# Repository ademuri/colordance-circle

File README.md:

# Colordance Circle

An art project that uses arrays of colored lights around a circle to create
kaleidoscopic colored shadows.

"This is not an officially supported Google product"

## Building

This project uses two build systems, PlatformIO and CMake. PIO is for code which
runs on embedded devices - these run the actual hardware. CMake is for running
tests on standard PCs.

To build with PlatformIO, run `pio run -e <env>`, where `<env>` is one defined
in [platformio.ini](platformio.ini) (e.g. `teensy`).

To run the tests:

```
mkdir -p build
cd build
cmake .. -DBUILD_SIMULATOR=false
make && ./generictest
```

### Simulator

The simulator uses SDL2 to render the LEDs. To build it, first install the SDL2 development library

`sudo apt install libsdl2-dev`

then, from the `build` directory, configure CMake to build it with

`cmake .. -DBUILD_SIMULATOR=true`

then build and run it with

`make && ./lib/simulator/Simulator`

#### Processing

To run the simulator with the Processing controller, from the build directory run:

```bash
${PROCESSING_HOME?}/processing-java --sketch=../controller/processing_controller --run | ./lib/simulator/Simulator
```

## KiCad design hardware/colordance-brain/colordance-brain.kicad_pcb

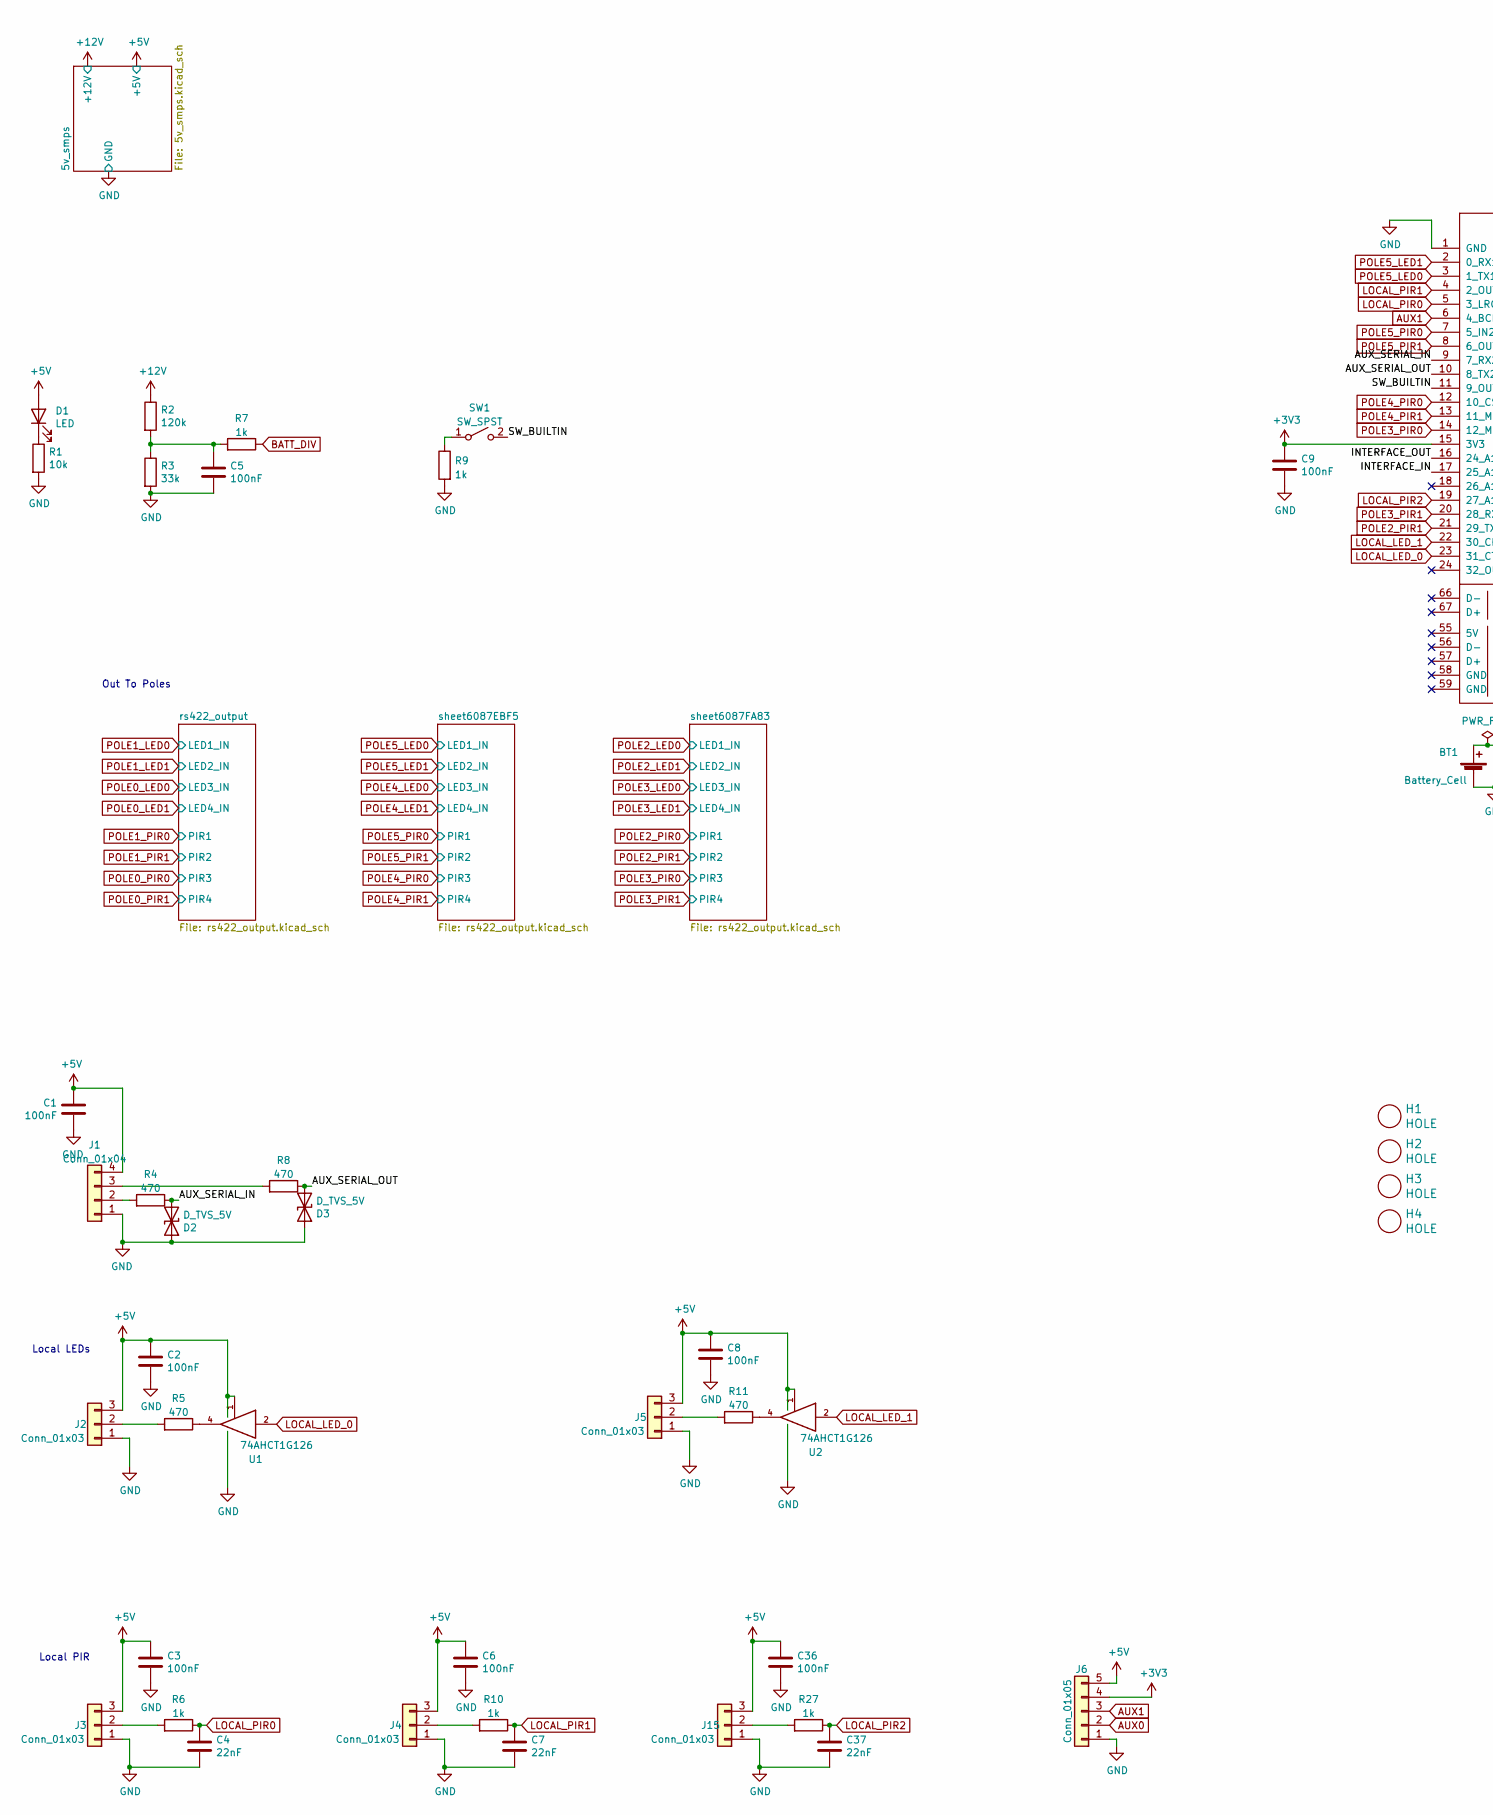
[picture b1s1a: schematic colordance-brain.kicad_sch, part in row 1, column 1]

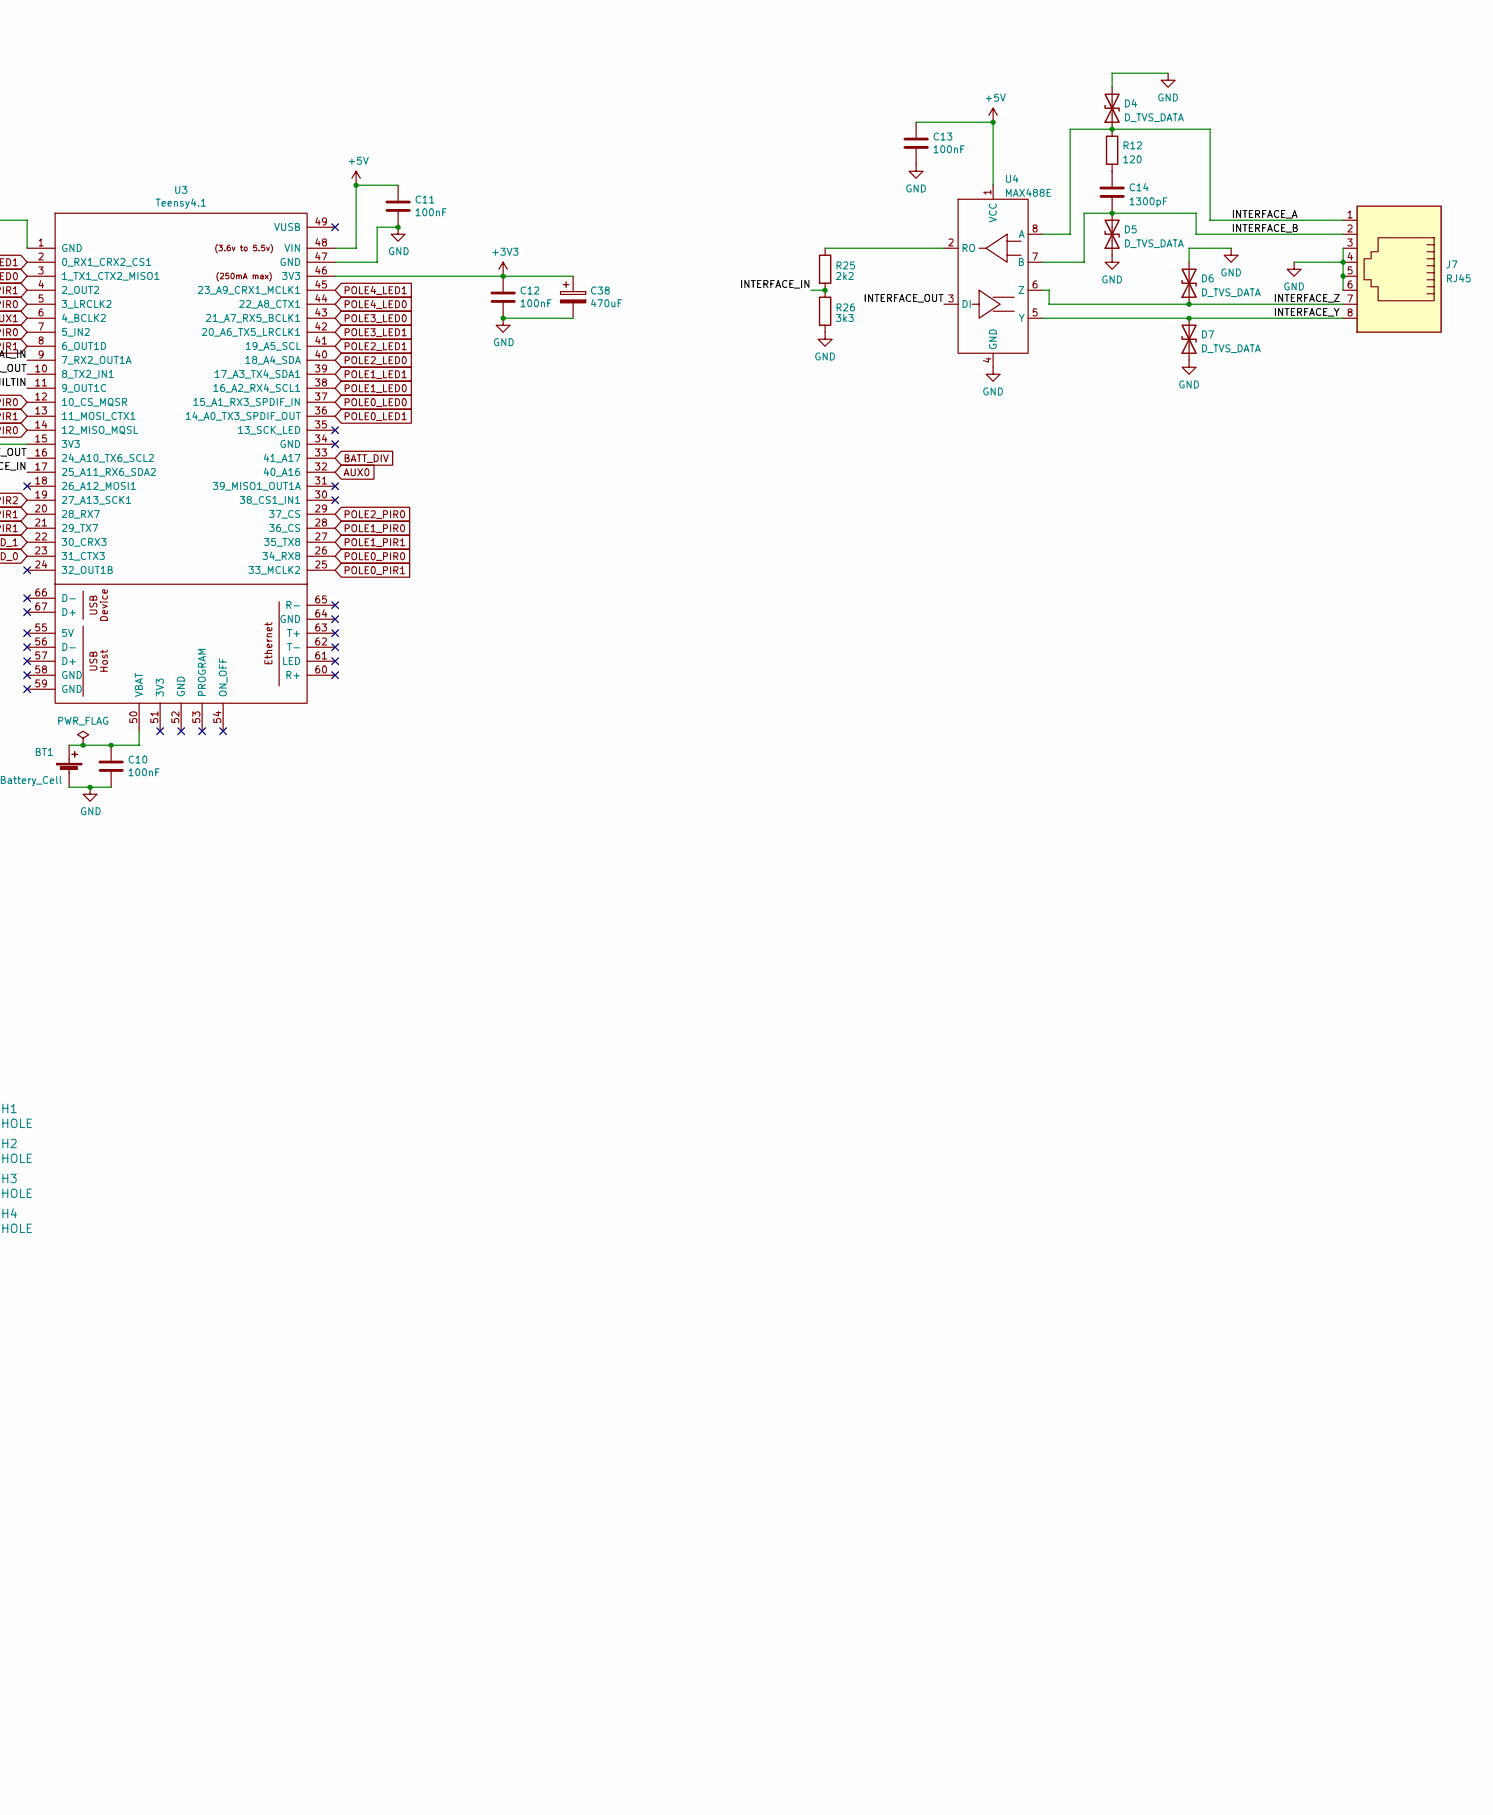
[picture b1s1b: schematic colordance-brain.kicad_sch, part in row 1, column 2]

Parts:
BT1: Battery_Cell; BatteryHolder_Keystone_3034_1x20mm; MPN 3034
C1, C2, C3, C5, C6, C8, C9, C10, C11, C12, C13, C36: 100nF; C_0402_1005Metric; LCSC C307331
C4, C7, C37: 22nF; C_0603_1608Metric; LCSC C21122
C14: 1300pF; C_0603_1608Metric; LCSC C1595
C38: 470uF; CP_Radial_D10.0mm_P5.00mm; MPN ESC477M035AH4EA
D1: LED; LED_0603_1608Metric; MPN 150060RS75000; LCSC C2286
D2, D3: D_TVS_5V; D_SMB; MPN SMBJ6.0CD-M3/H; LCSC C78395
D4, D5, D6, D7: D_TVS_DATA; D_SMB; MPN SMBJ6.0CD-M3/H; LCSC C78395
H1, H2, H3, H4: HOLE; HOLE_5MM_#8
J1: Conn_01x04; PinHeader_1x04_P2.54mm_Horizontal
J2, J3, J4, J5, J15: Conn_01x03; PinHeader_1x03_P2.54mm_Horizontal; MPN 78208-103HLF
J6: Conn_01x05; PinHeader_1x05_P2.54mm_Horizontal
J7: RJ45; RJ45_Amphenol_54602-x08_Horizontal; MPN 54601-908WPLF
R1: 10k; R_0603_1608Metric; LCSC C25804
R2: 120k; R_0603_1608Metric; MPN RG2012P-125-B-T5; LCSC C25808
R3: 33k; R_0603_1608Metric; MPN RT0603BRD07330KL; LCSC C4216
R4, R5, R8, R11: 470; R_0603_1608Metric; LCSC C23179
R6, R7, R9, R10, R27: 1k; R_0603_1608Metric; LCSC C21190
R12: 120; R_0603_1608Metric; LCSC C22787
R25: 2k2; R_0603_1608Metric; LCSC C4190
R26: 3k3; R_0603_1608Metric; LCSC C22978
SW1: SW_SPST; SW_PUSH_6mm
U1, U2: 74AHCT1G126; SOT-23-5; MPN 74AHCT1G126SE-7; LCSC C163712
U3: Teensy4.1; Teensy41_stripped; MPN PPPC241LFBN-RC
U4: MAX488E; SOIC-8_3.9x4.9mm_P1.27mm; LCSC C10919

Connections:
+3V3: C9.1, C12.1, C38.1, J6.4, U3.15 (3V3), U3.46 (3V3)
+5V: C1.1, C2.1, C3.1, C6.1, C8.1, C11.1, C13.1, C36.1, D1.2 (A), J1.4, J2.3, J3.3, J4.3, J5.3, J6.5, J15.3, U1.1, U1.5 (VCC), U2.1, U2.5 (VCC), U3.48 (VIN), U4.1 (VCC); also elsewhere on the board
+12V: R2.1; also elsewhere on the board
/AUX_SERIAL_IN: D2.2 (A2), R4.1, U3.9 (7_RX2_OUT1A)
/AUX_SERIAL_OUT: D3.2 (A2), R8.1, U3.10 (8_TX2_IN1)
/INTERFACE_A: D4.1 (A1), J7.1, R12.1, U4.8 (A)
/INTERFACE_B: C14.2, D5.2 (A2), J7.2, U4.7 (B)
/INTERFACE_IN: R25.2, R26.1, U3.17 (25_A11_RX6_SDA2)
/INTERFACE_OUT: U3.16 (24_A10_TX6_SCL2), U4.3 (DI)
/INTERFACE_Y: D7.2 (A2), J7.8, U4.5 (Y)
/INTERFACE_Z: D6.1 (A1), J7.7, U4.6 (Z)
/SW_BUILTIN: SW1.2 (B), U3.11 (9_OUT1C)
AUX0: J6.2, U3.32 (40_A16)
AUX1: J6.3, U3.6 (4_BCLK2)
BATT_DIV: R7.1, U3.33 (41_A17)
GND: BT1.2 (-), C1.2, C2.2, C3.2, C4.2, C5.2, C6.2, C7.2, C8.2, C9.2, C10.2, C11.2, C12.2, C13.2, C36.2, C37.2, C38.2, D2.1 (A1), D3.1 (A1), D4.2 (A2), D5.1 (A1), D6.2 (A2), D7.1 (A1), J1.1, J2.1, J3.1, J4.1, J5.1, J6.1, J7.3, J7.4, J7.5, J7.6, J15.1, R1.2, R3.2, R9.2, R26.2, U1.3 (GND), U2.3 (GND), U3.1 (GND), U3.47 (GND), U4.4 (GND); also elsewhere on the board
LOCAL_LED_0: U1.2, U3.23 (31_CTX3)
LOCAL_LED_1: U2.2, U3.22 (30_CRX3)
LOCAL_PIR0: C4.1, R6.1, U3.5 (3_LRCLK2)
LOCAL_PIR1: C7.1, R10.1, U3.4 (2_OUT2)
LOCAL_PIR2: C37.1, R27.1, U3.19 (27_A13_SCK1)
unnamed: BT1.1 (+), C10.1, U3.50 (VBAT)
unnamed: C5.1, R2.2, R3.1, R7.2
unnamed: C14.1, R12.2
unnamed: D1.1 (K), R1.1
unnamed: J1.2, R4.2
unnamed: J1.3, R8.2
unnamed: J2.2, R5.2
unnamed: J3.2, R6.2
unnamed: J4.2, R10.2
unnamed: J5.2, R11.2
unnamed: J15.2, R27.2
unnamed: R5.1, U1.4
unnamed: R11.1, U2.4
unnamed: R9.1, SW1.1 (A)
unnamed: R25.1, U4.2 (RO)
POLE0_LED0: U3.37 (15_A1_RX3_SPDIF_IN); also elsewhere on the board
POLE0_LED1: U3.36 (14_A0_TX3_SPDIF_OUT); also elsewhere on the board
POLE0_PIR0: U3.26 (34_RX8); also elsewhere on the board
POLE0_PIR1: U3.25 (33_MCLK2); also elsewhere on the board
POLE1_LED0: U3.38 (16_A2_RX4_SCL1); also elsewhere on the board
POLE1_LED1: U3.39 (17_A3_TX4_SDA1); also elsewhere on the board
POLE1_PIR0: U3.28 (36_CS); also elsewhere on the board
POLE1_PIR1: U3.27 (35_TX8); also elsewhere on the board
POLE2_LED0: U3.40 (18_A4_SDA); also elsewhere on the board
POLE2_LED1: U3.41 (19_A5_SCL); also elsewhere on the board
POLE2_PIR0: U3.29 (37_CS); also elsewhere on the board
POLE2_PIR1: U3.21 (29_TX7); also elsewhere on the board
POLE3_LED0: U3.43 (21_A7_RX5_BCLK1); also elsewhere on the board
POLE3_LED1: U3.42 (20_A6_TX5_LRCLK1); also elsewhere on the board
POLE3_PIR0: U3.14 (12_MISO_MQSL); also elsewhere on the board
POLE3_PIR1: U3.20 (28_RX7); also elsewhere on the board
POLE4_LED0: U3.44 (22_A8_CTX1); also elsewhere on the board
POLE4_LED1: U3.45 (23_A9_CRX1_MCLK1); also elsewhere on the board
POLE4_PIR0: U3.12 (10_CS_MQSR); also elsewhere on the board
POLE4_PIR1: U3.13 (11_MOSI_CTX1); also elsewhere on the board
POLE5_LED0: U3.3 (1_TX1_CTX2_MISO1); also elsewhere on the board
POLE5_LED1: U3.2 (0_RX1_CRX2_CS1); also elsewhere on the board
POLE5_PIR0: U3.7 (5_IN2); also elsewhere on the board
POLE5_PIR1: U3.8 (6_OUT1D); also elsewhere on the board

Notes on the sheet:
Local LEDs
Out To Poles
Local PIR

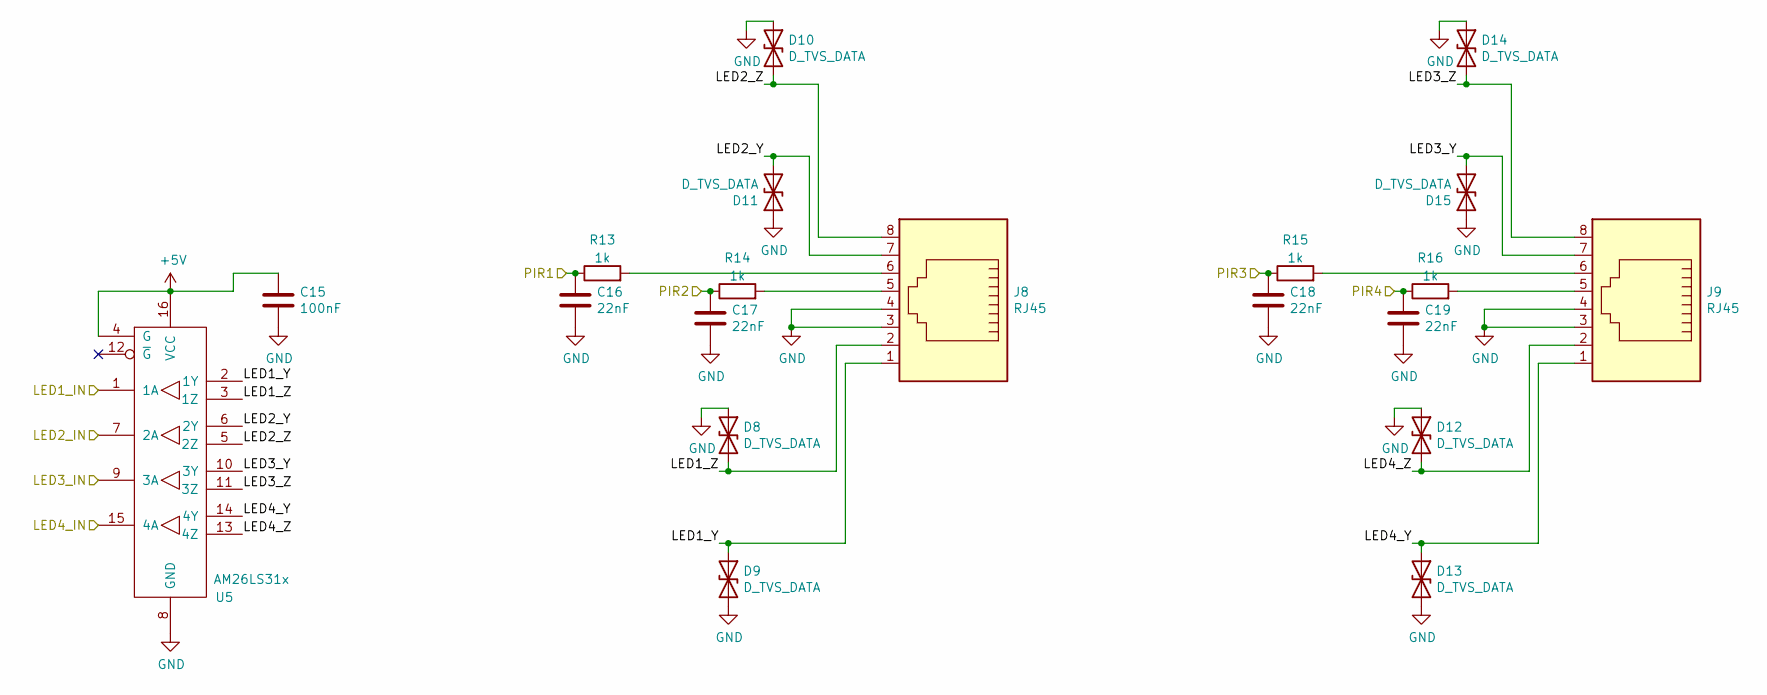
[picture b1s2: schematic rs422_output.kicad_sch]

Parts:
C15: 100nF; C_0402_1005Metric; LCSC C307331
C16, C17, C18, C19: 22nF; C_0603_1608Metric; LCSC C21122
D8, D9, D10, D11, D12, D13, D14, D15: D_TVS_DATA; D_SMB; MPN SMBJ6.0CD-M3/H; LCSC C78395
J8, J9: RJ45; RJ45_Amphenol_54602-x08_Horizontal; MPN 54601-908WPLF
R13, R14, R15, R16: 1k; R_0603_1608Metric; LCSC C21190
U5: AM26LS31x; SOIC-16_3.9x9.9mm_P1.27mm; MPN AM26LS31CDR; LCSC C6179

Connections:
+5V: C15.1, U5.4 (G), U5.16 (VCC); also elsewhere on the board
/rs422_output/LED1_Y: D9.1 (A1), J8.1, U5.2 (1Y)
/rs422_output/LED1_Z: D8.2 (A2), J8.2, U5.3 (1Z)
/rs422_output/LED2_Y: D11.2 (A2), J8.7, U5.6 (2Y)
/rs422_output/LED2_Z: D10.2 (A2), J8.8, U5.5 (2Z)
/rs422_output/LED3_Y: D15.2 (A2), J9.7, U5.10 (3Y)
/rs422_output/LED3_Z: D14.2 (A2), J9.8, U5.11 (3Z)
/rs422_output/LED4_Y: D13.1 (A1), J9.1, U5.14 (4Y)
/rs422_output/LED4_Z: D12.2 (A2), J9.2, U5.13 (4Z)
GND: C15.2, C16.2, C17.2, C18.2, C19.2, D8.1 (A1), D9.2 (A2), D10.1 (A1), D11.1 (A1), D12.1 (A1), D13.2 (A2), D14.1 (A1), D15.1 (A1), J8.3, J8.4, J9.3, J9.4, U5.8 (GND); also elsewhere on the board
unnamed: J8.5, R14.2
unnamed: J8.6, R13.2
unnamed: J9.5, R16.2
unnamed: J9.6, R15.2
POLE0_LED0: U5.9 (3A); also elsewhere on the board
POLE0_LED1: U5.15 (4A); also elsewhere on the board
POLE0_PIR0: C18.1, R15.1; also elsewhere on the board
POLE0_PIR1: C19.1, R16.1; also elsewhere on the board
POLE1_LED0: U5.1 (1A); also elsewhere on the board
POLE1_LED1: U5.7 (2A); also elsewhere on the board
POLE1_PIR0: C16.1, R13.1; also elsewhere on the board
POLE1_PIR1: C17.1, R14.1; also elsewhere on the board

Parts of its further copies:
C20, C25: 100nF; C_0402_1005Metric; LCSC C307331
C21, C22, C23, C24, C26, C27, C28, C29: 22nF; C_0603_1608Metric; LCSC C21122
D16, D17, D18, D19, D20, D21, D22, D23, D24, D25, D26, D27, D28, D29, D30, D31: D_TVS_DATA; D_SMB; MPN SMBJ6.0CD-M3/H; LCSC C78395
J10, J11, J12, J13: RJ45; RJ45_Amphenol_54602-x08_Horizontal; MPN 54601-908WPLF
R17, R18, R19, R20, R21, R22, R23, R24: 1k; R_0603_1608Metric; LCSC C21190
U6, U7: AM26LS31x; SOIC-16_3.9x9.9mm_P1.27mm; MPN AM26LS31CDR; LCSC C6179

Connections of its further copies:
+5V: C20.1, C25.1, U6.4 (G), U6.16 (VCC), U7.4 (G), U7.16 (VCC); also elsewhere on the board
/sheet6087EBF5/LED1_Y: D17.1 (A1), J10.1, U6.2 (1Y)
/sheet6087EBF5/LED1_Z: D16.2 (A2), J10.2, U6.3 (1Z)
/sheet6087EBF5/LED2_Y: D19.2 (A2), J10.7, U6.6 (2Y)
/sheet6087EBF5/LED2_Z: D18.2 (A2), J10.8, U6.5 (2Z)
/sheet6087EBF5/LED3_Y: D23.2 (A2), J11.7, U6.10 (3Y)
/sheet6087EBF5/LED3_Z: D22.2 (A2), J11.8, U6.11 (3Z)
/sheet6087EBF5/LED4_Y: D21.1 (A1), J11.1, U6.14 (4Y)
/sheet6087EBF5/LED4_Z: D20.2 (A2), J11.2, U6.13 (4Z)
/sheet6087FA83/LED1_Y: D25.1 (A1), J12.1, U7.2 (1Y)
/sheet6087FA83/LED1_Z: D24.2 (A2), J12.2, U7.3 (1Z)
/sheet6087FA83/LED2_Y: D27.2 (A2), J12.7, U7.6 (2Y)
/sheet6087FA83/LED2_Z: D26.2 (A2), J12.8, U7.5 (2Z)
/sheet6087FA83/LED3_Y: D31.2 (A2), J13.7, U7.10 (3Y)
/sheet6087FA83/LED3_Z: D30.2 (A2), J13.8, U7.11 (3Z)
/sheet6087FA83/LED4_Y: D29.1 (A1), J13.1, U7.14 (4Y)
/sheet6087FA83/LED4_Z: D28.2 (A2), J13.2, U7.13 (4Z)
GND: C20.2, C21.2, C22.2, C23.2, C24.2, C25.2, C26.2, C27.2, C28.2, C29.2, D16.1 (A1), D17.2 (A2), D18.1 (A1), D19.1 (A1), D20.1 (A1), D21.2 (A2), D22.1 (A1), D23.1 (A1), D24.1 (A1), D25.2 (A2), D26.1 (A1), D27.1 (A1), D28.1 (A1), D29.2 (A2), D30.1 (A1), D31.1 (A1), J10.3, J10.4, J11.3, J11.4, J12.3, J12.4, J13.3, J13.4, U6.8 (GND), U7.8 (GND); also elsewhere on the board
unnamed: J10.5, R18.2
unnamed: J10.6, R17.2
unnamed: J11.5, R20.2
unnamed: J11.6, R19.2
unnamed: J12.5, R22.2
unnamed: J12.6, R21.2
unnamed: J13.5, R24.2
unnamed: J13.6, R23.2
POLE2_LED0: U7.1 (1A); also elsewhere on the board
POLE2_LED1: U7.7 (2A); also elsewhere on the board
POLE2_PIR0: C26.1, R21.1; also elsewhere on the board
POLE2_PIR1: C27.1, R22.1; also elsewhere on the board
POLE3_LED0: U7.9 (3A); also elsewhere on the board
POLE3_LED1: U7.15 (4A); also elsewhere on the board
POLE3_PIR0: C28.1, R23.1; also elsewhere on the board
POLE3_PIR1: C29.1, R24.1; also elsewhere on the board
POLE4_LED0: U6.9 (3A); also elsewhere on the board
POLE4_LED1: U6.15 (4A); also elsewhere on the board
POLE4_PIR0: C23.1, R19.1; also elsewhere on the board
POLE4_PIR1: C24.1, R20.1; also elsewhere on the board
POLE5_LED0: U6.1 (1A); also elsewhere on the board
POLE5_LED1: U6.7 (2A); also elsewhere on the board
POLE5_PIR0: C21.1, R17.1; also elsewhere on the board
POLE5_PIR1: C22.1, R18.1; also elsewhere on the board

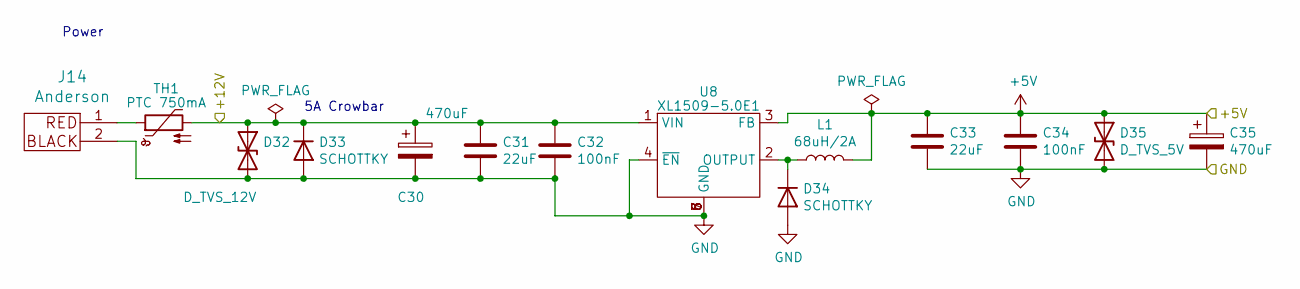
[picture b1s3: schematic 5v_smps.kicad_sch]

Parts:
C30, C35: 470uF; CP_Radial_D10.0mm_P5.00mm; MPN ESC477M035AH4EA
C31, C33: 22uF; C_0805_2012Metric; MPN LMK212BBJ226MG-T; LCSC C45783
C32, C34: 100nF; C_0402_1005Metric; LCSC C307331
D32: D_TVS_12V; D_SMB; MPN SMBJ13CA; LCSC C1976713
D33, D34: SCHOTTKY; D_SMA; LCSC C22452
D35: D_TVS_5V; D_SMB; MPN SMBJ6.0CD-M3/H; LCSC C78395
J14: Anderson; Anderson_1336G1_right_angle_bottom_two
L1: 68uH/2A; L_PROD-Tech_PSPMAA0805; LCSC C2962891
TH1: PTC 750mA; Fuse_1812_4532Metric; LCSC C20997
U8: XL1509-5.0E1; SOIC-8_3.9x4.9mm_P1.27mm; LCSC C61063

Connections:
+5V: C33.1, C34.1, C35.1, D35.1 (A1), L1.2, U8.3 (FB); also elsewhere on the board
+12V: C30.1, C31.1, C32.1, D32.1 (A1), D33.1 (K), TH1.2, U8.1 (VIN); also elsewhere on the board
GND: C30.2, C31.2, C32.2, C33.2, C34.2, C35.2, D32.2 (A2), D33.2 (A), D34.2 (A), D35.2 (A2), J14.2, U8.4 (~EN), U8.5 (GND), U8.6 (GND), U8.7 (GND), U8.8 (GND); also elsewhere on the board
unnamed: D34.1 (K), L1.1, U8.2 (OUTPUT)
unnamed: J14.1, TH1.1

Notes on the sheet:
Power
5A Crowbar

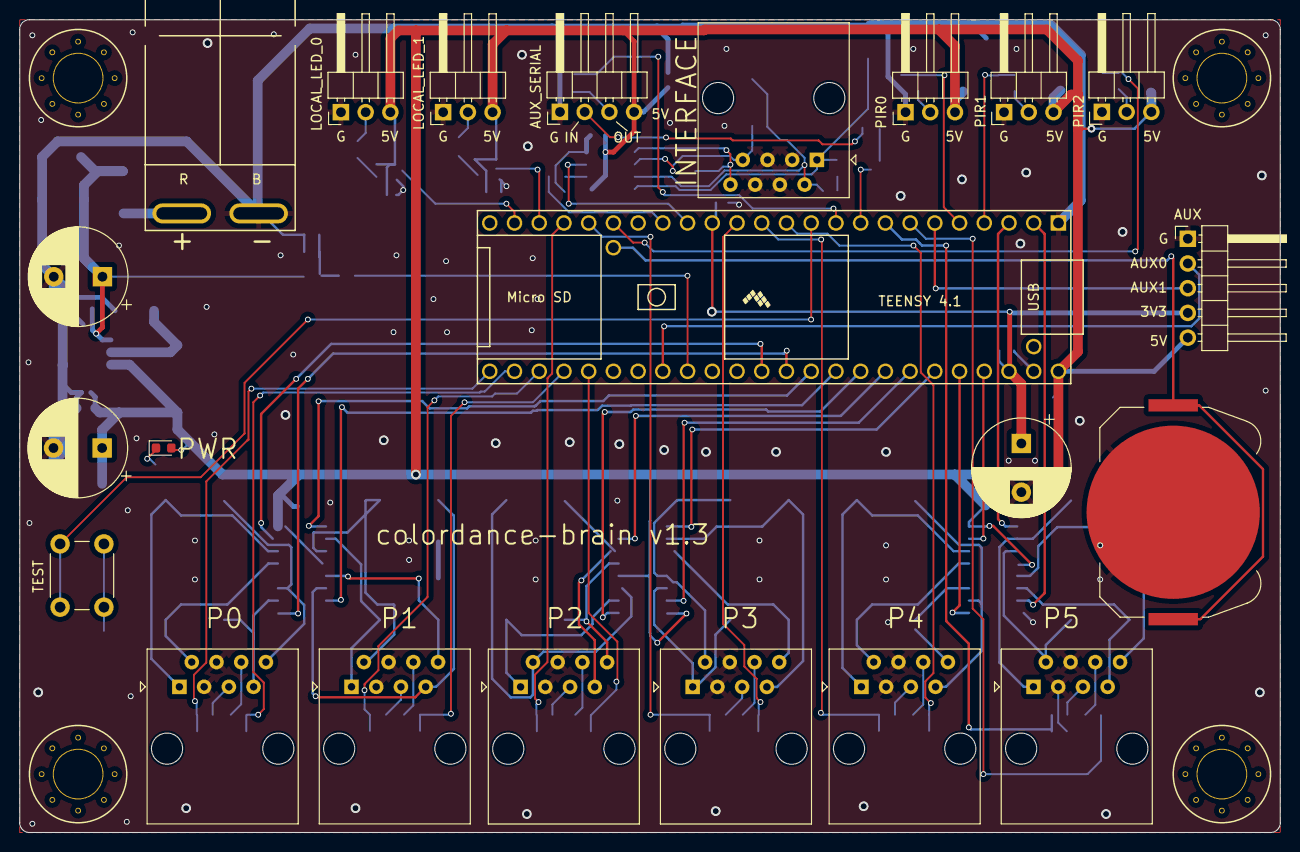
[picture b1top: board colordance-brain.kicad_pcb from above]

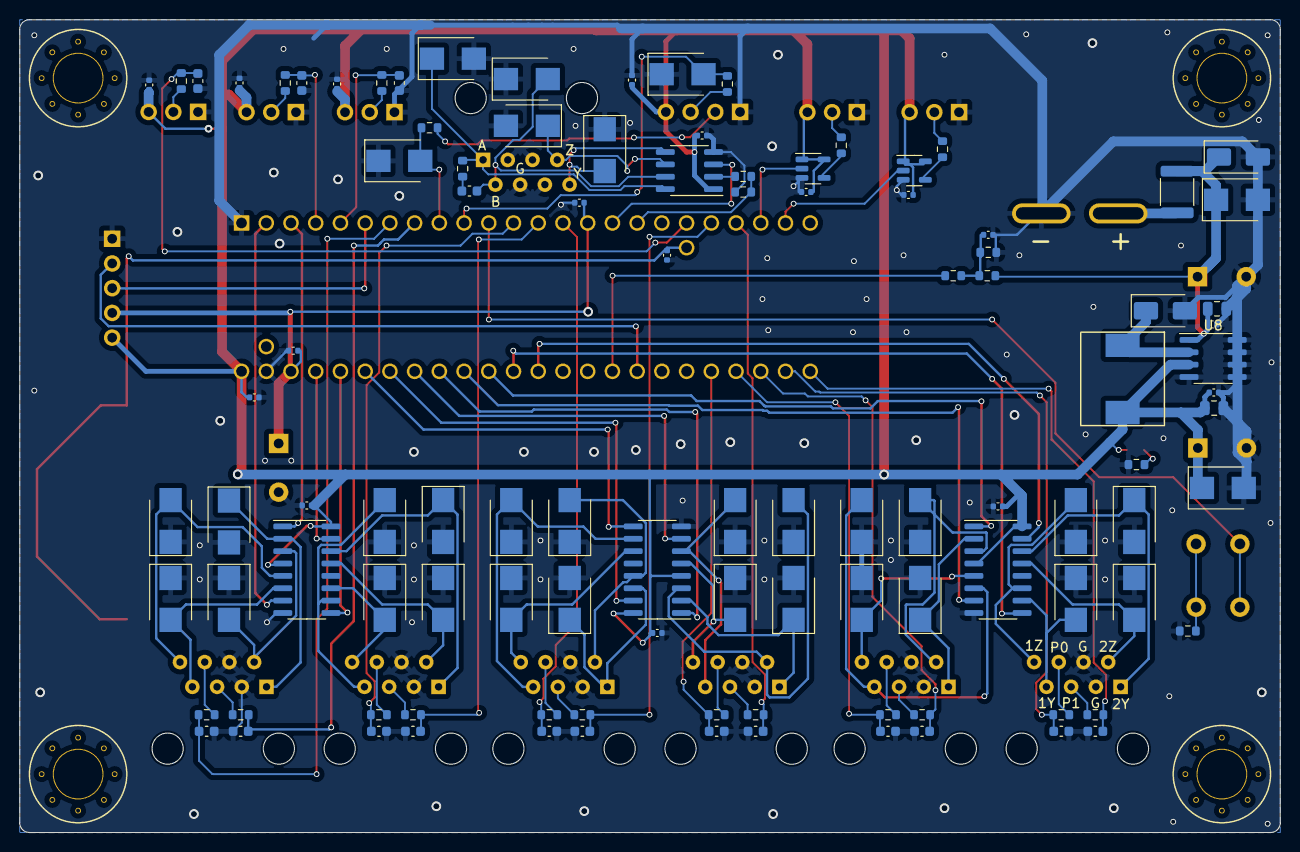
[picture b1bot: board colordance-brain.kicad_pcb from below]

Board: 2 copper layers, 129.5 x 83.5 mm, 131 parts (105 on the bottom side), 98 nets.

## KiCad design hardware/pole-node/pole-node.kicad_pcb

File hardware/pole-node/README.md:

## Datasheets

- APA3211: [datasheet](https://www.diodes.com/assets/Datasheets/AP3211.pdf), [application notes](https://www.diodes.com/assets/Part-Support-Files/AP3211/6434133.pdf)

## Calculations

### Voltage regulator

- Feedback voltage is 0.81V. Use [this voltage divider calculator](http://www.ti.com/download/kbase/volt/volt_div3.htm). For E96, this yields 11500 and 2210 Ohms, which produces 5.02v.
- Inductor value: `L1 = 5V * (12V - 5V) / (1.4MHz * 12V * 1.5A * .26) = 5.3uH -> 5.6 uH`
- Peak inductor current: `1.5A + ((12V - 5V) * 5V) / (2 * 1.4MHz * 12V * 5.6uH) = 1.69A`
- Inductor current rating is `1.5 * 1.69A = 2.5A`
- Input ripple with 10uF cap: `1.5A / (1.4Mhz * 10uF) * (5V / 12V) * (1 - (5V / 12V)) = .026V`

### RS485 termination

- [Application note](http://www.ti.com/lit/an/snla034b/snla034b.pdf)
- AC termination should yield clean signal without significantly increasing power consumption
- Assuming 40' max cable length:
- `C<sub>T <= (40ft * 2 * 1.7ns/ft) / 100 Ohm = 1.36 nF`
- This yields an RC time constant of `136 ns`. At `800 kHz`, the signal period is `1.25 us`.

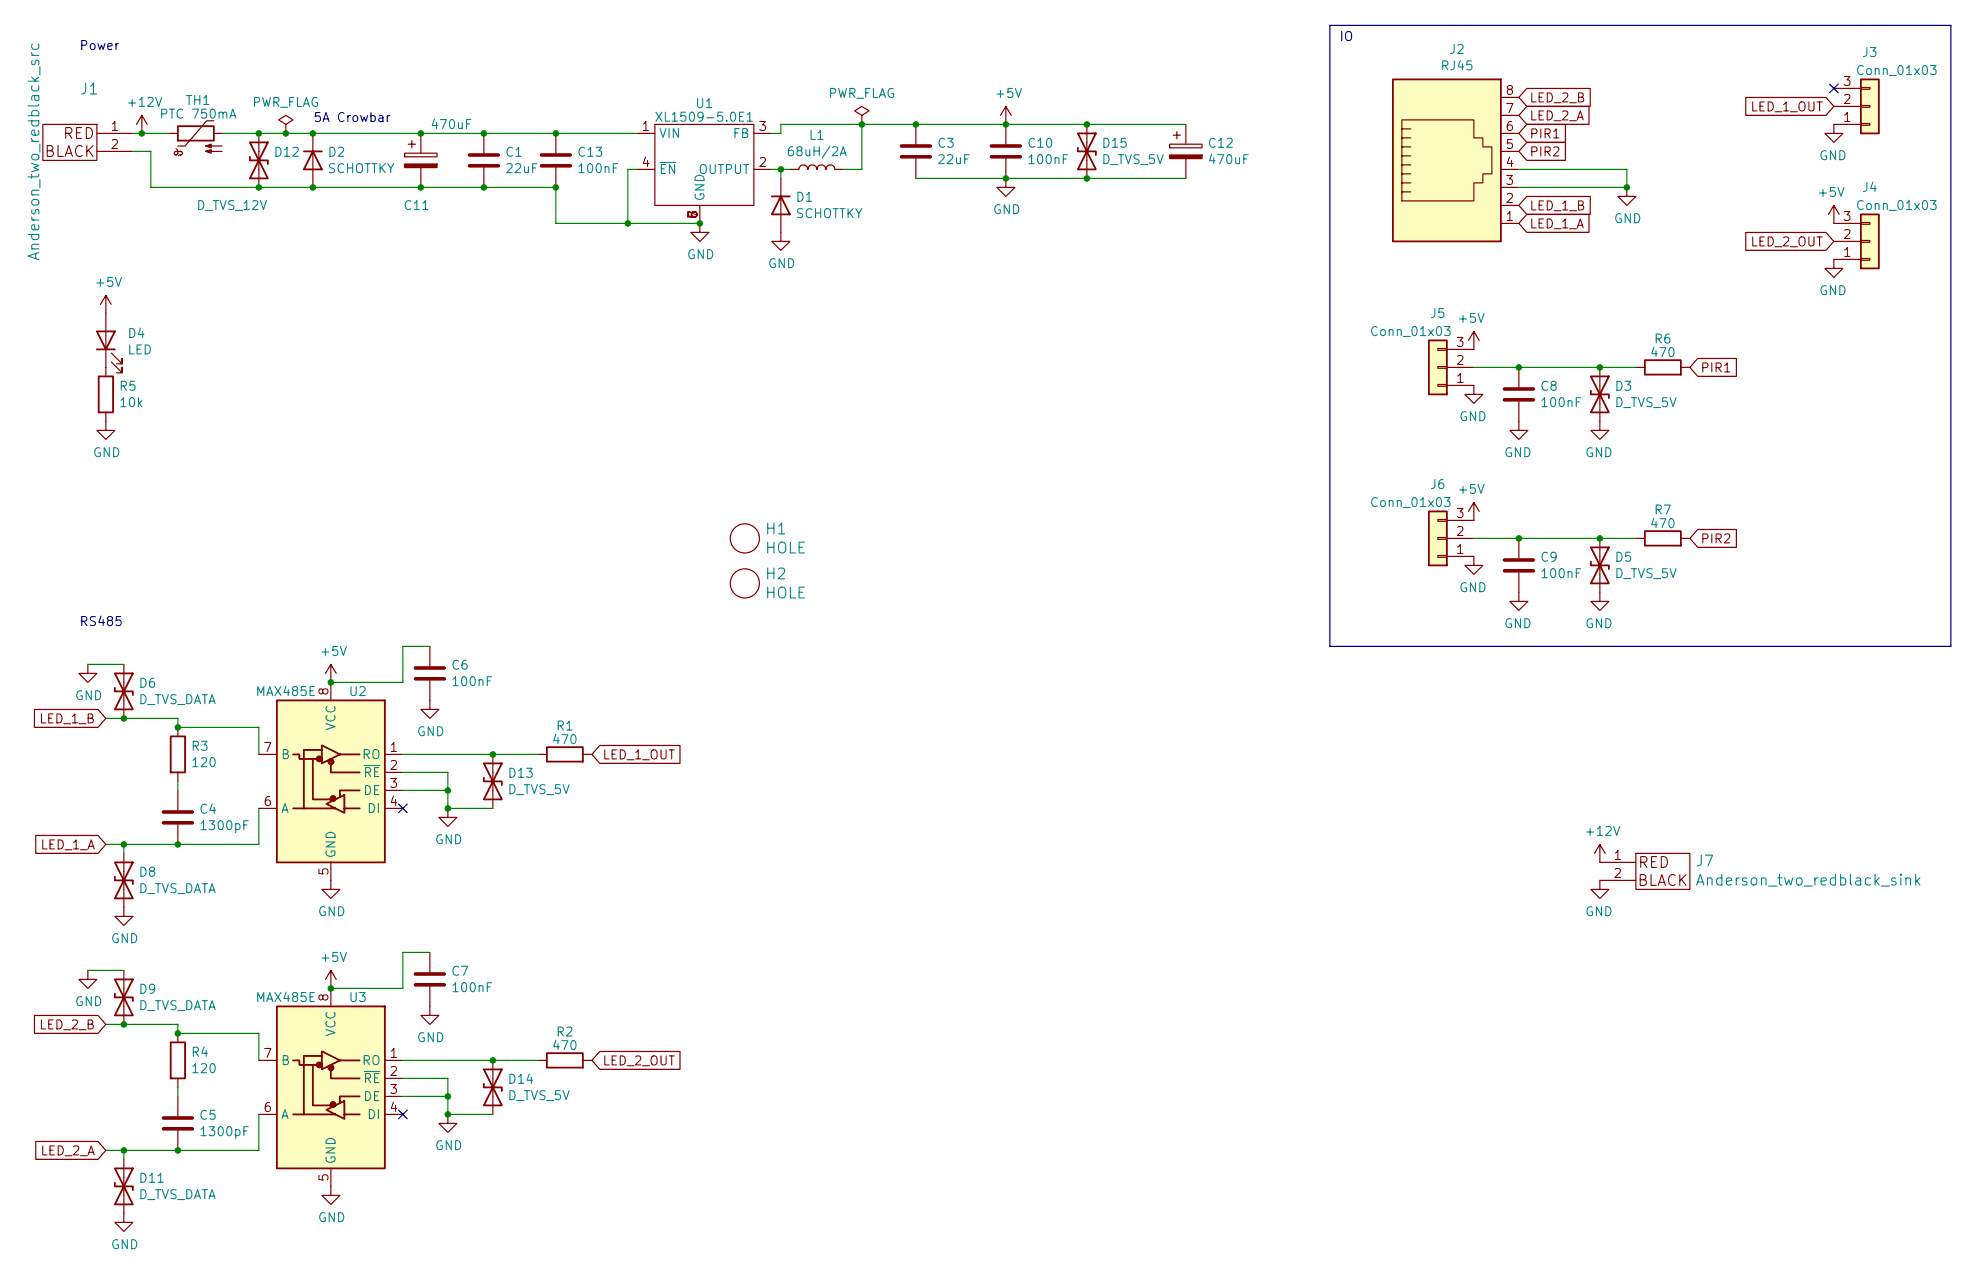
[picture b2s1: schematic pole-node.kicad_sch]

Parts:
C1, C3: 22uF; C_0805_2012Metric; MPN LMK212BBJ226MG-T; LCSC C45783
C4, C5: 1300pF; C_0603_1608Metric; MPN CL10B122KB8NNNC; LCSC C1595
C6, C7, C8, C9, C10, C13: 100nF; C_0402_1005Metric; LCSC C307331
C11, C12: 470uF; CP_Radial_D10.0mm_P5.00mm; MPN ESC477M035AH4EA
D1, D2: SCHOTTKY; D_SMA; LCSC C22452
D3, D5, D13, D14, D15: D_TVS_5V; D_SMB; MPN SMBJ6.0CD-M3/H; LCSC C78395
D4: LED; LED_0603_1608Metric; MPN 150060RS75000; LCSC C2286
D6, D8, D9, D11: D_TVS_DATA; D_SMB; MPN SMBJ6.0CD-M3/H; LCSC C78395
D12: D_TVS_12V; D_SMB; MPN SMBJ13CA; LCSC C1976713
H1, H2: HOLE
J1: Anderson_two_redblack_src
J2: RJ45; RJ45_Amphenol_54602-x08_Horizontal; MPN 54601-908WPLF
J3, J4, J5, J6: Conn_01x03; PinHeader_1x03_P2.54mm_Horizontal; MPN 78208-103HLF
J7: Anderson_two_redblack_sink
L1: 68uH/2A; L_PROD-Tech_PSPMAA0805; LCSC C2962891
R1, R2, R6, R7: 470; R_0603_1608Metric; LCSC C23179
R3, R4: 120; R_0603_1608Metric; MPN RMCF0603JG120R; LCSC C22787
R5: 10k; R_0603_1608Metric; LCSC C25804
TH1: PTC 750mA; Fuse_1812_4532Metric; LCSC C20997
U1: XL1509-5.0E1; SOIC-8_3.9x4.9mm_P1.27mm; LCSC C61063
U2, U3: MAX485E; SOIC-8_3.9x4.9mm_P1.27mm; MPN SP485ECN-L/TR; LCSC C916163

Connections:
+5V: C3.1, C6.1, C7.1, C10.1, C12.1, D4.2 (A), D15.1 (A1), J4.3, J5.3, J6.3, L1.2, U1.3 (FB), U2.8 (VCC), U3.8 (VCC)
+12V: J1.1, J7.1, TH1.1
GND: C1.2, C3.2, C6.2, C7.2, C8.2, C9.2, C10.2, C11.2, C12.2, C13.2, D1.2 (A), D2.2 (A), D3.2 (A2), D5.2 (A2), D6.1 (A1), D8.2 (A2), D9.1 (A1), D11.2 (A2), D12.2 (A2), D13.2 (A2), D14.2 (A2), D15.2 (A2), J1.2, J2.3, J2.4, J3.1, J4.1, J5.1, J6.1, J7.2, R5.2, U1.4 (~EN), U1.5 (GND), U1.6 (GND), U1.7 (GND), U1.8 (GND), U2.2 (~RE), U2.3 (DE), U2.5 (GND), U3.2 (~RE), U3.3 (DE), U3.5 (GND)
LED_1_A: C4.2, D8.1 (A1), J2.1, U2.6 (A)
LED_1_B: D6.2 (A2), J2.2, R3.1, U2.7 (B)
LED_1_OUT: J3.2, R1.2
LED_2_A: C5.2, D11.1 (A1), J2.7, U3.6 (A)
LED_2_B: D9.2 (A2), J2.8, R4.1, U3.7 (B)
LED_2_OUT: J4.2, R2.2
unnamed: C1.1, C11.1, C13.1, D2.1 (K), D12.1 (A1), TH1.2, U1.1 (VIN)
unnamed: C4.1, R3.2
unnamed: C5.1, R4.2
unnamed: D1.1 (K), L1.1, U1.2 (OUTPUT)
unnamed: C8.1, D3.1 (A1), J5.2, R6.1
unnamed: D4.1 (K), R5.1
unnamed: C9.1, D5.1 (A1), J6.2, R7.1
unnamed: D13.1 (A1), R1.1, U2.1 (RO)
unnamed: D14.1 (A1), R2.1, U3.1 (RO)
PIR1: J2.6, R6.2
PIR2: J2.5, R7.2

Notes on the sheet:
Power
5A Crowbar
RS485

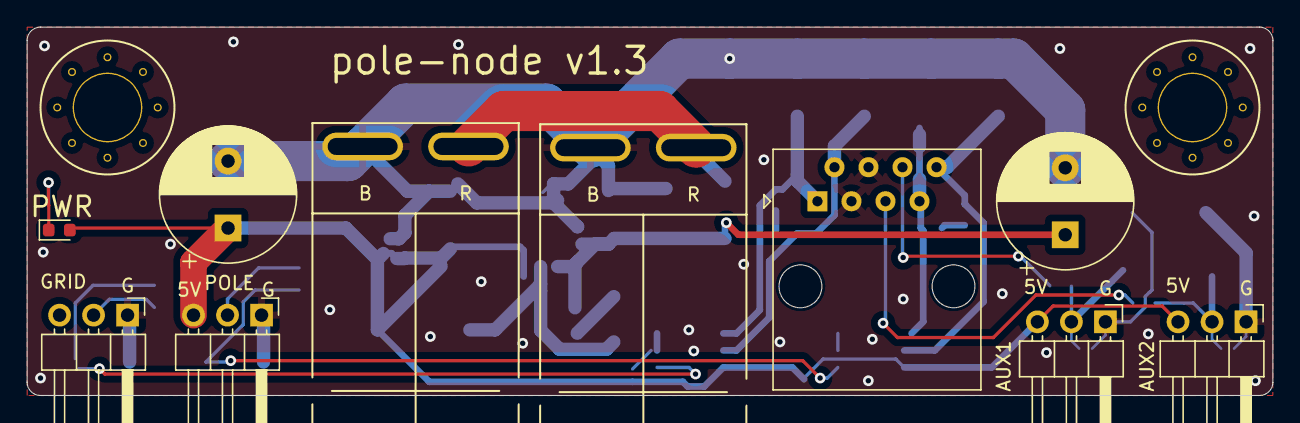
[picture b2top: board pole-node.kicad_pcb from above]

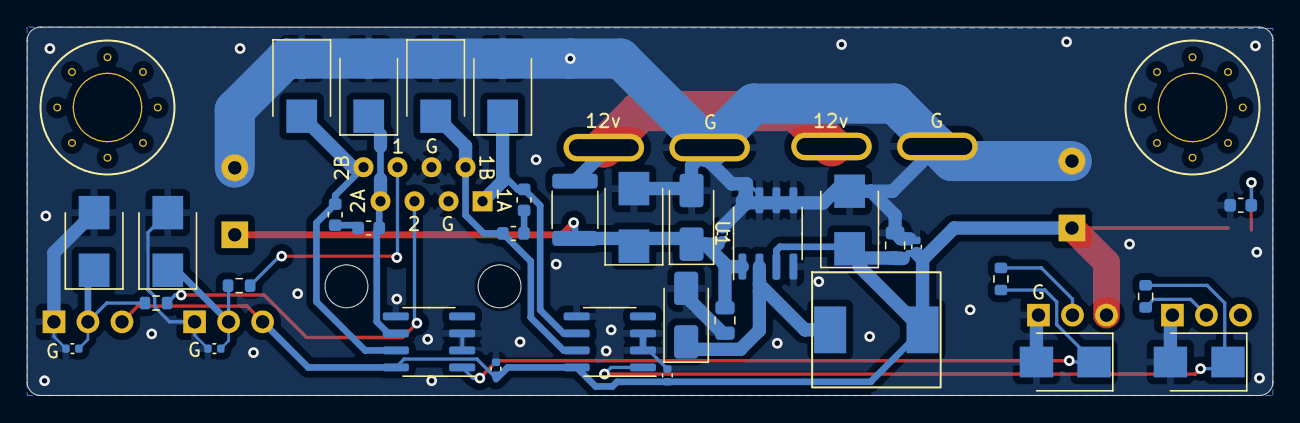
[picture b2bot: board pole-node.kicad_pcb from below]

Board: 2 copper layers, 93.0 x 27.5 mm, 46 parts (34 on the bottom side), 20 nets.
